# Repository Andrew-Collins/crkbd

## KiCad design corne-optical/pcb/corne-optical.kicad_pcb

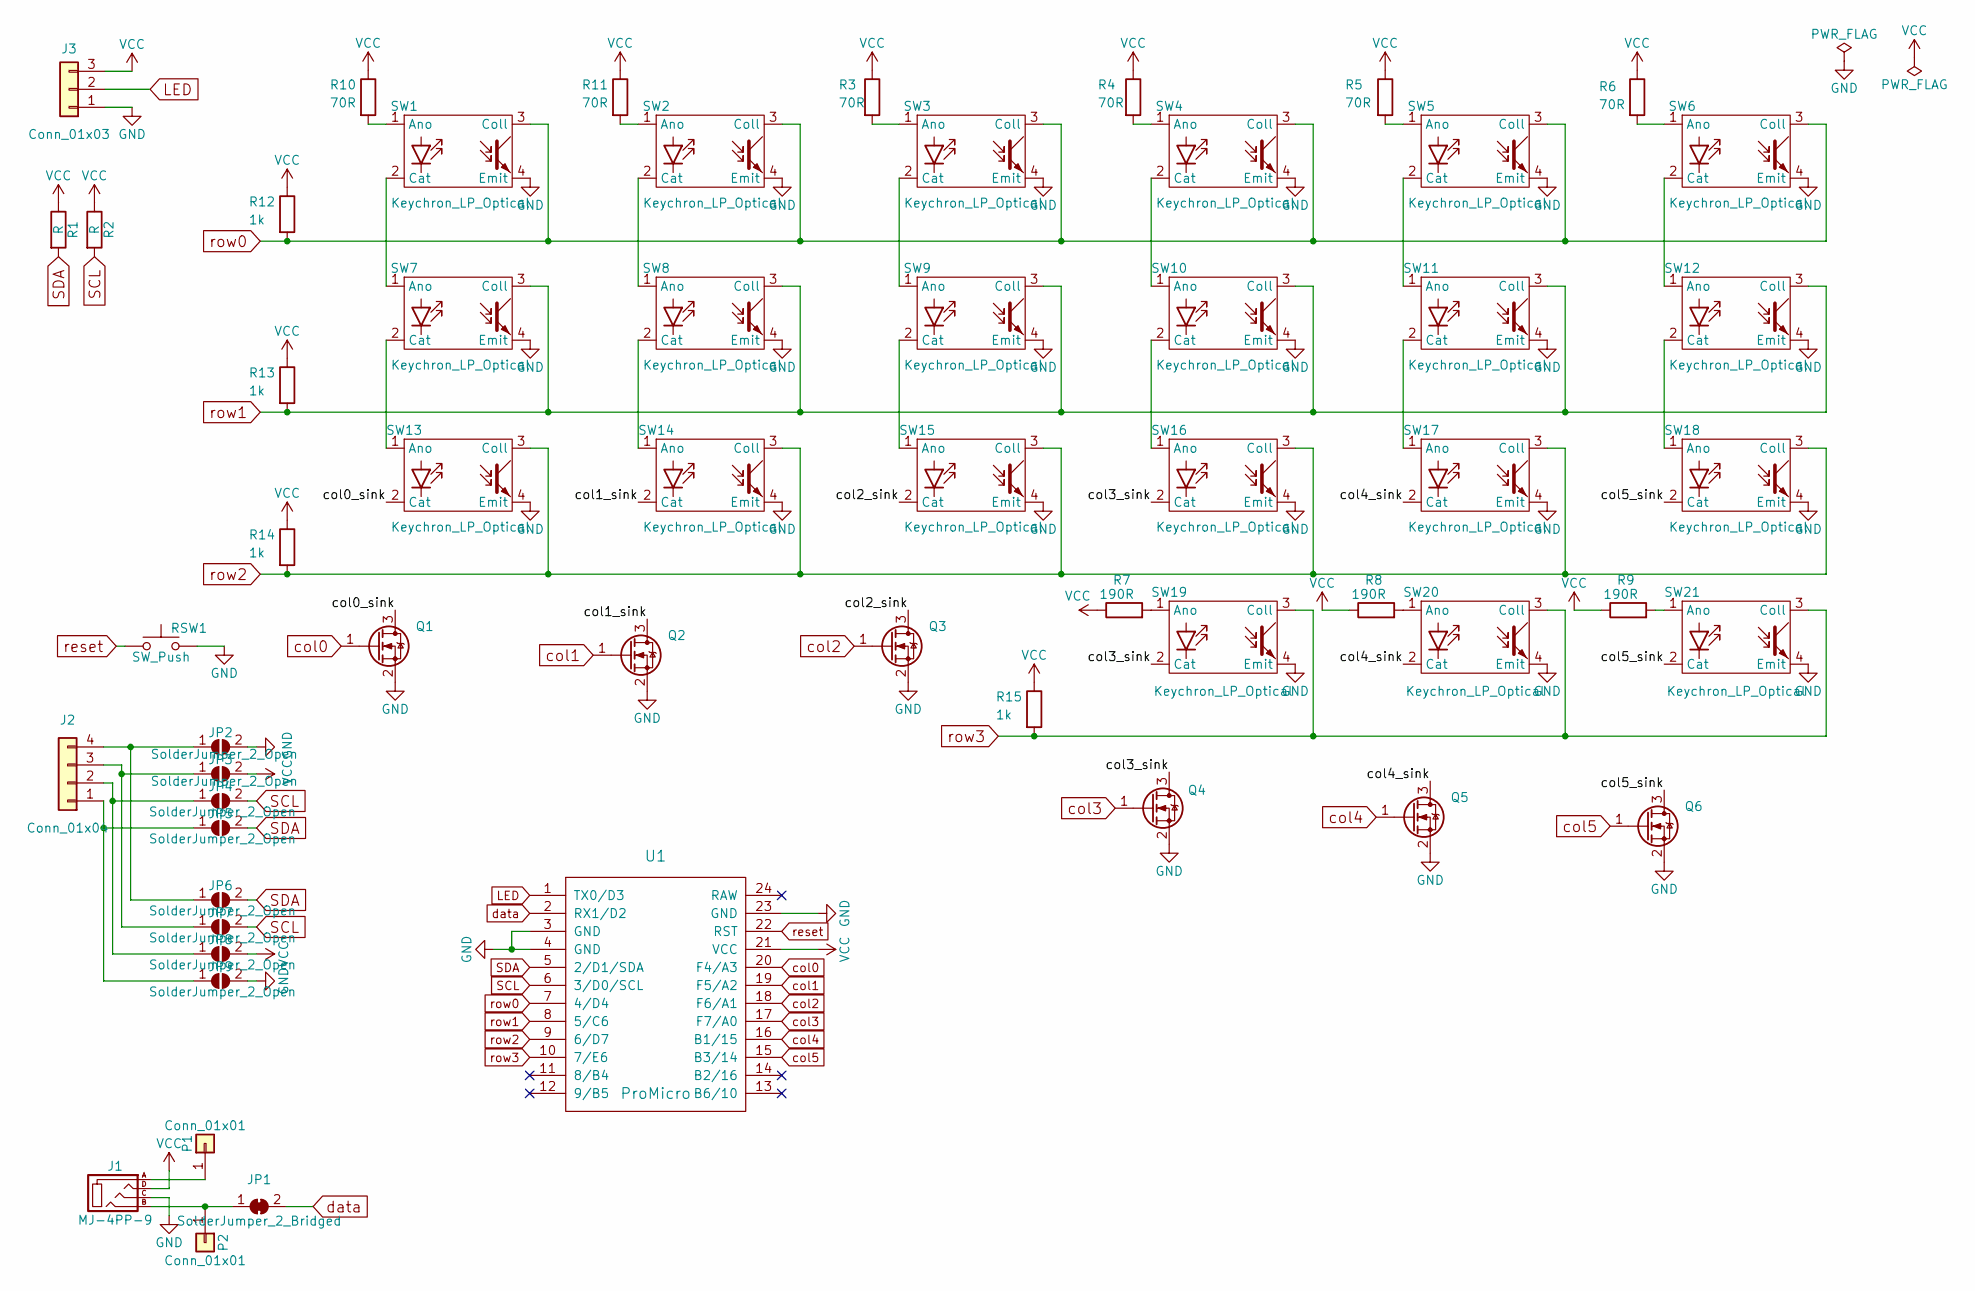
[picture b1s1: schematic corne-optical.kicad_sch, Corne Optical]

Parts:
J1: MJ-4PP-9
J2: Conn_01x04; OLED
J3: Conn_01x03; StripLED_rev
JP1: SolderJumper_2_Bridged; Jumper
JP2, JP3, JP4, JP5, JP6, JP7, JP8, JP9: SolderJumper_2_Open; Jumper
P1, P2: Conn_01x01; 1pin_conn
Q1, Q2, Q3, Q4, Q5, Q6: Q_NMOS_GSD; SOT-23
R1, R2: R; R_0603_1608Metric
R3, R4, R5, R6, R10, R11: 70R; R_0603_1608Metric
R7, R8, R9: 190R; R_0603_1608Metric
R12, R13, R14, R15: 1k; R_0603_1608Metric
RSW1: SW_Push; ResetSW
SW1, SW2, SW3, SW4, SW5, SW6, SW7, SW8, SW9, SW10, SW11, SW12, SW13, SW14, SW15, SW16, SW17, SW18, SW19, SW20: Keychron_LP_Optical
SW21: Keychron_LP_Optical; Keychron_LP_Optical_1.5u
U1: ProMicro; ProMicro_v2

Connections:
/col0_sink: Q1.3 (D), SW13.2 (Cat)
/col1_sink: Q2.3 (D), SW14.2 (Cat)
/col2_sink: Q3.3 (D), SW15.2 (Cat)
/col3_sink: Q4.3 (D), SW16.2 (Cat), SW19.2 (Cat)
/col4_sink: Q5.3 (D), SW17.2 (Cat), SW20.2 (Cat)
/col5_sink: Q6.3 (D), SW18.2 (Cat), SW21.2 (Cat)
GND: J1.C, J3.1, JP2.2 (B), JP9.2 (B), Q1.2 (S), Q2.2 (S), Q3.2 (S), Q4.2 (S), Q5.2 (S), Q6.2 (S), RSW1.2, SW1.4 (Emit), SW2.4 (Emit), SW3.4 (Emit), SW4.4 (Emit), SW5.4 (Emit), SW6.4 (Emit), SW7.4 (Emit), SW8.4 (Emit), SW9.4 (Emit), SW10.4 (Emit), SW11.4 (Emit), SW12.4 (Emit), SW13.4 (Emit), SW14.4 (Emit), SW15.4 (Emit), SW16.4 (Emit), SW17.4 (Emit), SW18.4 (Emit), SW19.4 (Emit), SW20.4 (Emit), SW21.4 (Emit), U1.3 (GND), U1.4 (GND), U1.23 (GND)
LED: J3.2, U1.1 (TX0/D3)
unnamed: J1.A, P1.1
unnamed: J1.B, JP1.1 (A), P2.1
unnamed: J2.1, JP5.1 (A), JP9.1 (A)
unnamed: J2.2, JP4.1 (A), JP8.1 (A)
unnamed: J2.3, JP3.1 (A), JP7.1 (A)
unnamed: J2.4, JP2.1 (A), JP6.1 (A)
unnamed: R3.2, SW3.1 (Ano)
unnamed: R4.2, SW4.1 (Ano)
unnamed: R5.2, SW5.1 (Ano)
unnamed: R6.2, SW6.1 (Ano)
unnamed: R7.2, SW19.1 (Ano)
unnamed: R8.2, SW20.1 (Ano)
unnamed: R9.2, SW21.1 (Ano)
unnamed: R10.2, SW1.1 (Ano)
unnamed: R11.2, SW2.1 (Ano)
unnamed: SW1.2 (Cat), SW7.1 (Ano)
unnamed: SW2.2 (Cat), SW8.1 (Ano)
unnamed: SW3.2 (Cat), SW9.1 (Ano)
unnamed: SW4.2 (Cat), SW10.1 (Ano)
unnamed: SW10.2 (Cat), SW16.1 (Ano)
unnamed: SW5.2 (Cat), SW11.1 (Ano)
unnamed: SW11.2 (Cat), SW17.1 (Ano)
unnamed: SW6.2 (Cat), SW12.1 (Ano)
unnamed: SW12.2 (Cat), SW18.1 (Ano)
unnamed: SW7.2 (Cat), SW13.1 (Ano)
unnamed: SW8.2 (Cat), SW14.1 (Ano)
unnamed: SW9.2 (Cat), SW15.1 (Ano)
SCL: JP4.2 (B), JP7.2 (B), R2.2, U1.6 (3/D0/SCL)
SDA: JP5.2 (B), JP6.2 (B), R1.2, U1.5 (2/D1/SDA)
VCC: J1.D, J3.3, JP3.2 (B), JP8.2 (B), R1.1, R2.1, R3.1, R4.1, R5.1, R6.1, R7.1, R8.1, R9.1, R10.1, R11.1, R12.1, R13.1, R14.1, R15.1, U1.21 (VCC)
col0: Q1.1 (G), U1.20 (F4/A3)
col1: Q2.1 (G), U1.19 (F5/A2)
col2: Q3.1 (G), U1.18 (F6/A1)
col3: Q4.1 (G), U1.17 (F7/A0)
col4: Q5.1 (G), U1.16 (B1/15)
col5: Q6.1 (G), U1.15 (B3/14)
data: JP1.2 (B), U1.2 (RX1/D2)
reset: RSW1.1, U1.22 (RST)
row0: R12.2, SW1.3 (Coll), SW2.3 (Coll), SW3.3 (Coll), SW4.3 (Coll), SW5.3 (Coll), SW6.3 (Coll), U1.7 (4/D4)
row1: R13.2, SW7.3 (Coll), SW8.3 (Coll), SW9.3 (Coll), SW10.3 (Coll), SW11.3 (Coll), SW12.3 (Coll), U1.8 (5/C6)
row2: R14.2, SW13.3 (Coll), SW14.3 (Coll), SW15.3 (Coll), SW16.3 (Coll), SW17.3 (Coll), SW18.3 (Coll), U1.9 (6/D7)
row3: R15.2, SW19.3 (Coll), SW20.3 (Coll), SW21.3 (Coll), U1.10 (7/E6)

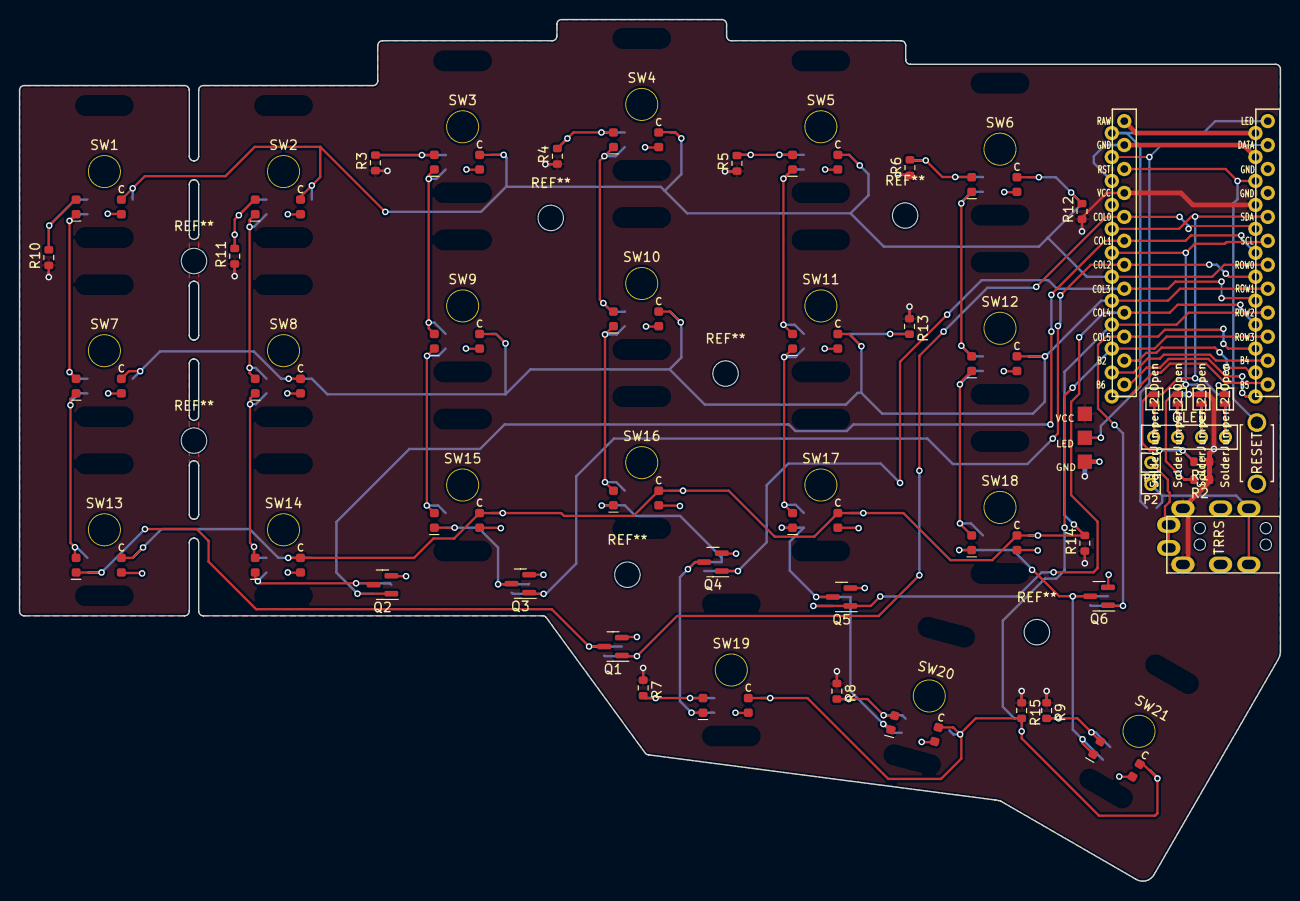
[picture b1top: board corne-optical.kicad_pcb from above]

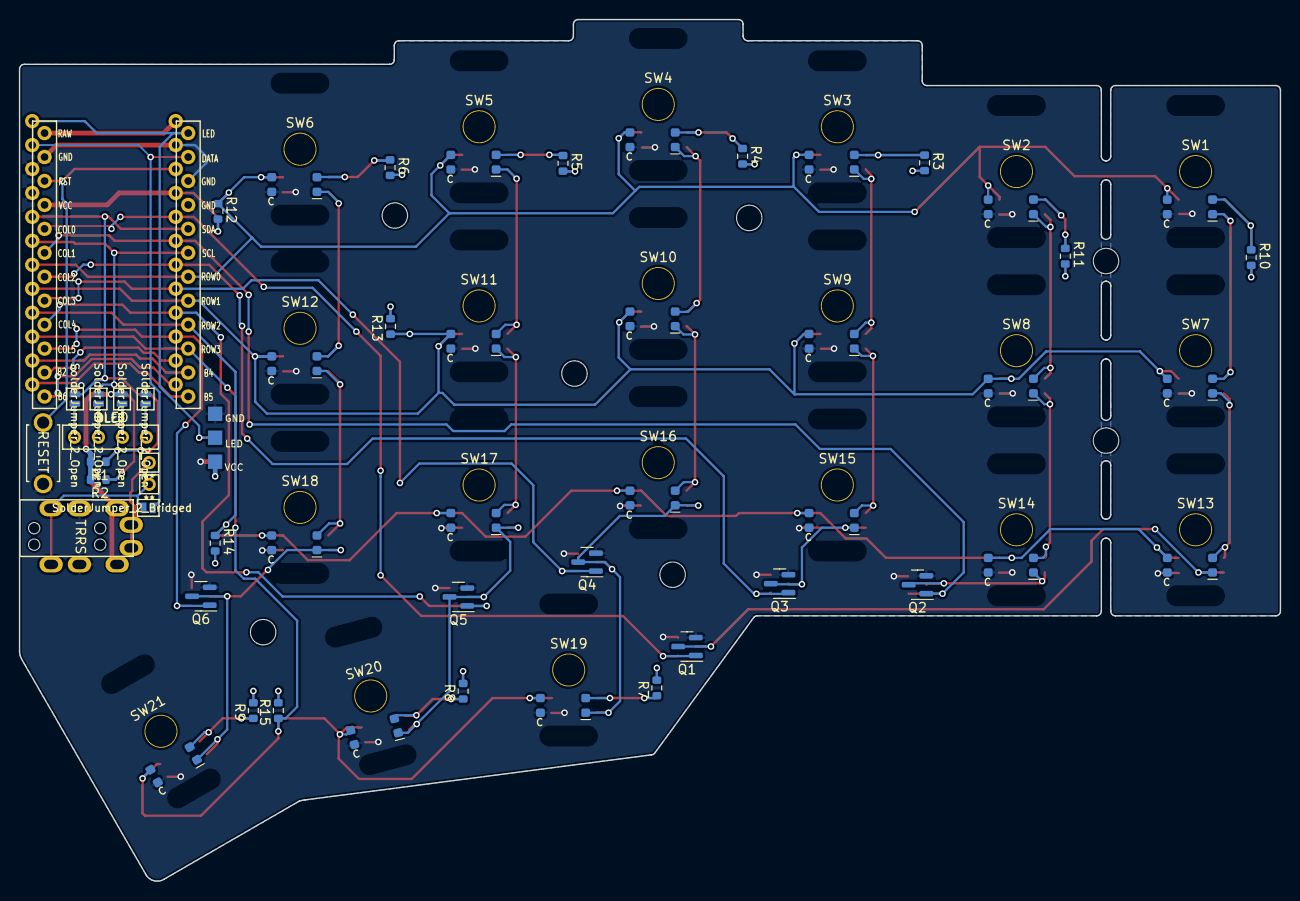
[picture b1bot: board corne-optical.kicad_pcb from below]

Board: 2 copper layers, 133.8 x 91.4 mm, 58 parts (5 on the bottom side), 50 nets.

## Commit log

2022-07-31 chocolate ready to go with extra connectors for travelling
2022-07-31 Optical schematic done
2022-07-31 Fixed up designators on optical
2022-07-31 Missed a few
2022-07-31 Trying to workout phantom copper
2022-08-03 Fixed outline, just trying to solve switch footprint glitch
2022-08-07 Finished, but need to add mounting holes for plate
2022-08-21 Holes done and board sent off
2022-08-25 Added plates
